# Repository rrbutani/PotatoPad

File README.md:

# PotatoPad
A (potato-y) portable game console made using the TM4C Launchpad, duct tape, and magic.

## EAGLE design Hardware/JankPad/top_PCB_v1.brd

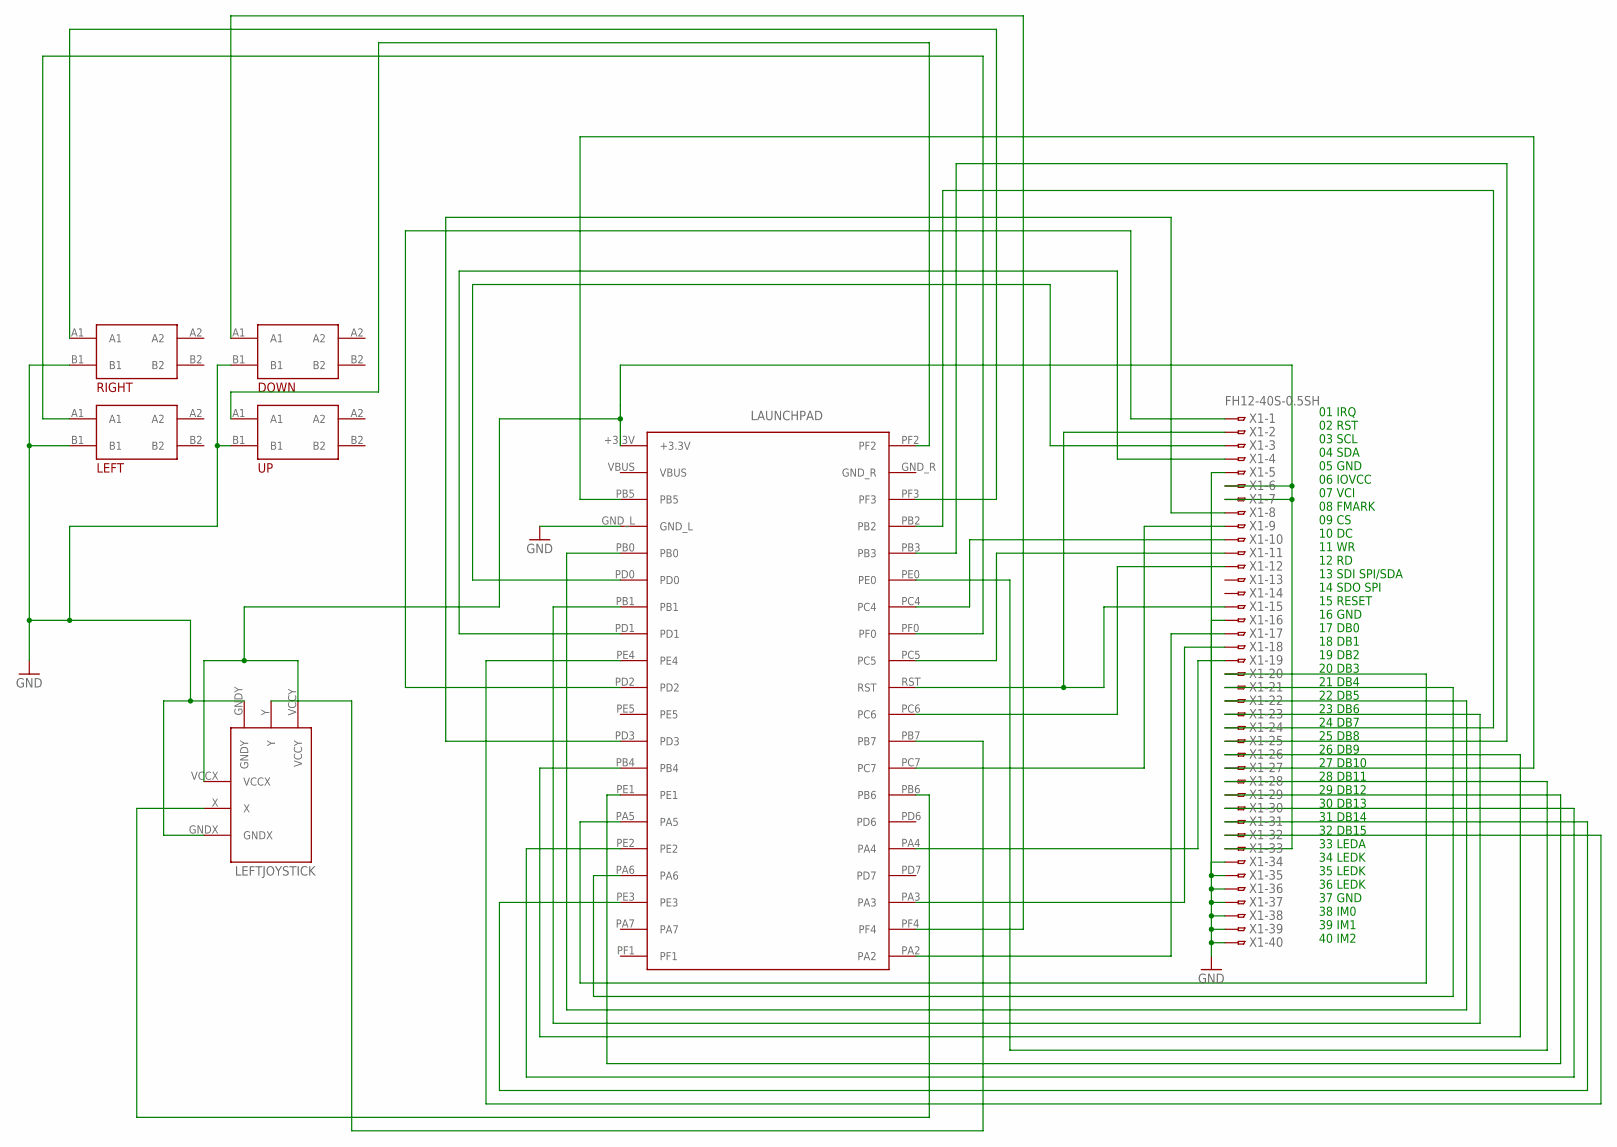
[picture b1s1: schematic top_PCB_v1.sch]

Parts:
DOWN: TACTILEBUTTONTHROUGHHOLE; B3F-40XX-MOD
LAUNCHPAD: TM4CTM4C; 1_05X2MM
LEFT: TACTILEBUTTONTHROUGHHOLE; B3F-40XX-MOD
LEFTJOYSTICK: JOYSTICKADAFRUIT; JOYSTICK
RIGHT: TACTILEBUTTONTHROUGHHOLE; B3F-40XX-MOD
UP: TACTILEBUTTONTHROUGHHOLE; B3F-40XX-MOD
X1: FH12-40S-0.5SH

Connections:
GND: DOWN.B1, LAUNCHPAD.GND_L, LEFT.B1, LEFTJOYSTICK.GNDX, LEFTJOYSTICK.GNDY, RIGHT.B1, UP.B1, X1.5, X1.16, X1.34, X1.35, X1.36, X1.37, X1.38, X1.39, X1.40
GND_R: LAUNCHPAD.GND_R
unnamed: LAUNCHPAD.PD3, X1.8
unnamed: LAUNCHPAD.RST, X1.2, X1.15
unnamed: LAUNCHPAD.PC4, X1.10
unnamed: LAUNCHPAD.PC5, X1.11
unnamed: LAUNCHPAD.PC6, X1.12
unnamed: LAUNCHPAD.PC7, X1.9
unnamed: LAUNCHPAD.PA2, X1.17
unnamed: LAUNCHPAD.PF2, UP.A1
unnamed: LAUNCHPAD.PD0, X1.3
unnamed: LAUNCHPAD.PD1, X1.4
unnamed: LAUNCHPAD.PD2, X1.1
unnamed: LAUNCHPAD.PA3, X1.18
unnamed: LAUNCHPAD.PA4, X1.19
unnamed: LAUNCHPAD.PA5, X1.20
unnamed: LAUNCHPAD.PA6, X1.21
unnamed: LAUNCHPAD.PB0, X1.22
unnamed: LAUNCHPAD.PB1, X1.23
unnamed: LAUNCHPAD.PB2, X1.24
unnamed: LAUNCHPAD.PB3, X1.25
unnamed: LAUNCHPAD.PB4, X1.26
unnamed: LAUNCHPAD.PB5, X1.27
unnamed: LAUNCHPAD.PE0, X1.28
unnamed: LAUNCHPAD.PE1, X1.29
unnamed: LAUNCHPAD.PE2, X1.30
unnamed: LAUNCHPAD.PE3, X1.31
unnamed: LAUNCHPAD.PE4, X1.32
unnamed: LAUNCHPAD.PB6, LEFTJOYSTICK.X
unnamed: LAUNCHPAD.PF0, LEFT.A1
unnamed: LAUNCHPAD.PF3, RIGHT.A1
unnamed: LAUNCHPAD.+3.3V, LEFTJOYSTICK.VCCX, LEFTJOYSTICK.VCCY, X1.6, X1.7, X1.33
unnamed: DOWN.A1, LAUNCHPAD.PF4
unnamed: LAUNCHPAD.PB7, LEFTJOYSTICK.Y
VBUS: LAUNCHPAD.VBUS

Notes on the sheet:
01 IRQ 02 RST 03 SCL 04 SDA 05 GND 06 IOVCC 07 VCI 08 FMARK 09 CS 10 DC 11 WR 12 RD 13 SDI SPI/SDA 14 SDO SPI 15 RESET 16 GND 17 DB0 18 DB1 19 DB2 20 DB3 21 DB4 22 DB5 23 DB6 24 DB7 25 DB8 26 DB9 27 DB10 28 DB11 29 DB12 30 DB13 31 DB14 32 DB15 33 LEDA 34 LEDK 35 LEDK 36 LEDK 37 GND 38 IM0 39 IM1 40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

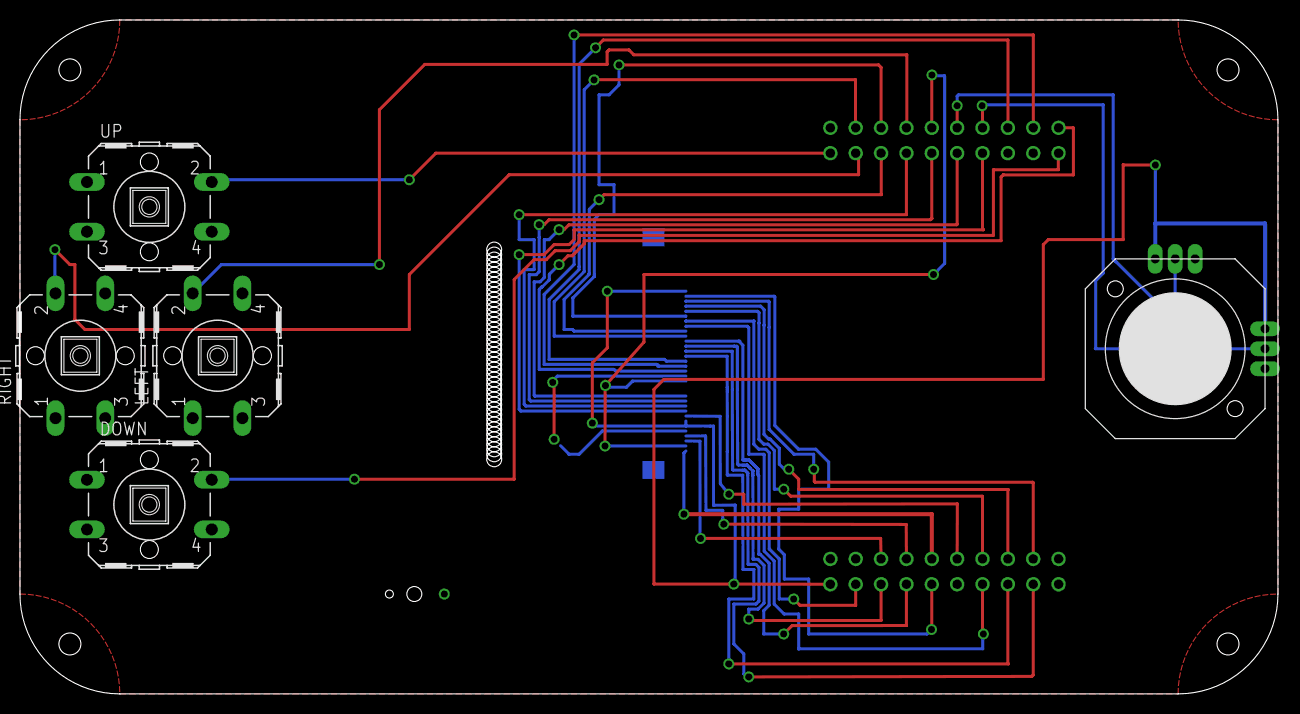
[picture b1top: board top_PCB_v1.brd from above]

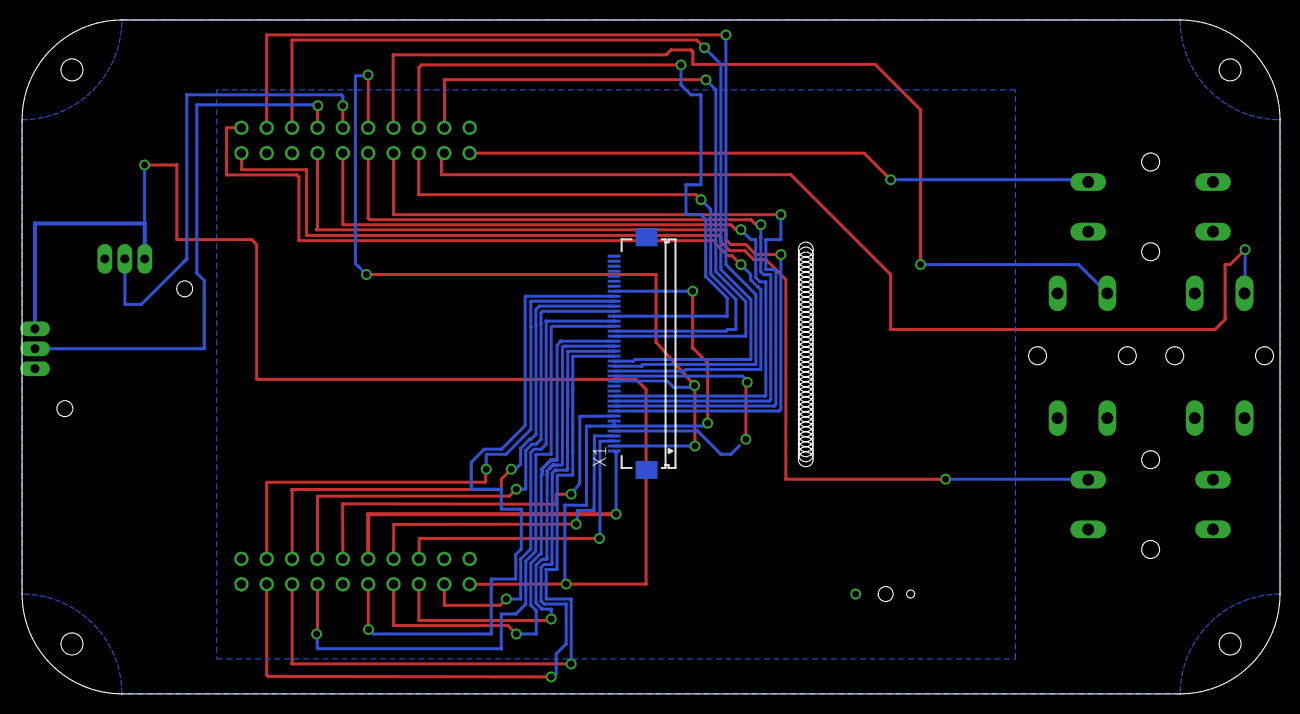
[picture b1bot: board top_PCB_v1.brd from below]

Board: 2 copper layers, 126.0 x 67.5 mm, 7 parts (2 on the bottom side), 33 nets.

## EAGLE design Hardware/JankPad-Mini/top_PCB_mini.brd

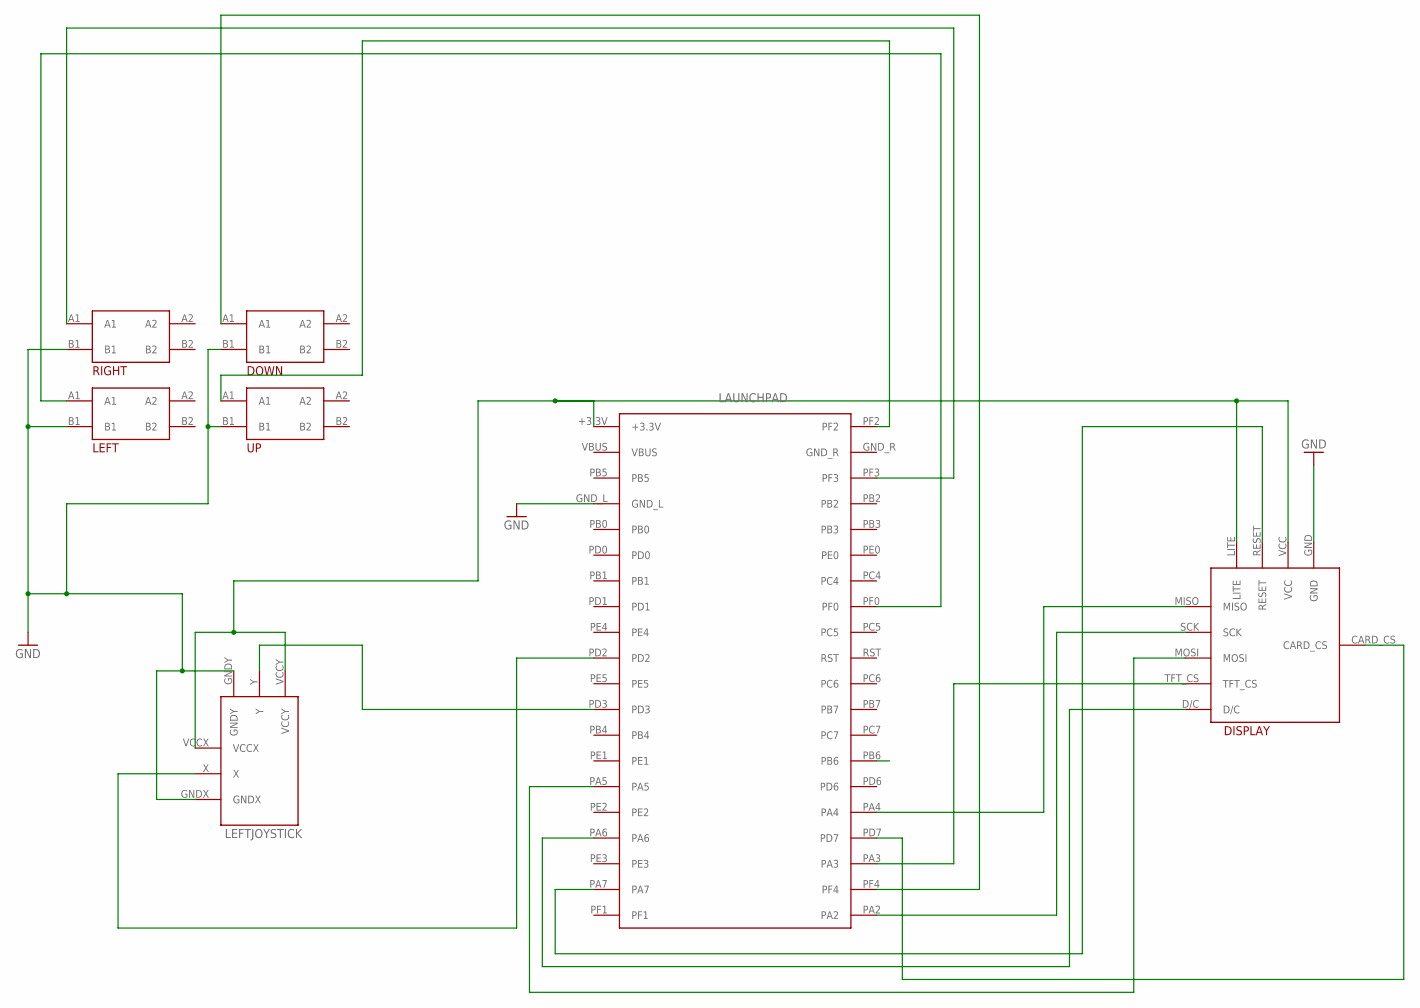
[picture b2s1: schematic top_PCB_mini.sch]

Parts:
DISPLAY: ADAFRUITST7735R_18
DOWN: TACTILEBUTTONTHROUGHHOLE; B3F-40XX-MOD
LAUNCHPAD: TM4CTM4C; 1_05X2MM
LEFT: TACTILEBUTTONTHROUGHHOLE; B3F-40XX-MOD
LEFTJOYSTICK: JOYSTICKADAFRUIT; JOYSTICK
RIGHT: TACTILEBUTTONTHROUGHHOLE; B3F-40XX-MOD
UP: TACTILEBUTTONTHROUGHHOLE; B3F-40XX-MOD

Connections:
GND: DISPLAY.GND, DOWN.B1, LAUNCHPAD.GND_L, LEFT.B1, LEFTJOYSTICK.GNDX, LEFTJOYSTICK.GNDY, RIGHT.B1, UP.B1
GND_R: LAUNCHPAD.GND_R
unnamed: DISPLAY.RESET, LAUNCHPAD.PA7
unnamed: DISPLAY.D/C, LAUNCHPAD.PA6
unnamed: DISPLAY.CARD_CS, LAUNCHPAD.PD7
unnamed: DISPLAY.TFT_CS, LAUNCHPAD.PA3
unnamed: DISPLAY.MOSI, LAUNCHPAD.PA5
unnamed: DISPLAY.SCK, LAUNCHPAD.PA2
unnamed: DISPLAY.MISO, LAUNCHPAD.PA4
unnamed: LAUNCHPAD.PF2, UP.A1
unnamed: LAUNCHPAD.PD2, LEFTJOYSTICK.X
unnamed: LAUNCHPAD.PD3, LEFTJOYSTICK.Y
unnamed: LAUNCHPAD.PF0, LEFT.A1
unnamed: LAUNCHPAD.PF3, RIGHT.A1
unnamed: DISPLAY.LITE, DISPLAY.VCC, LAUNCHPAD.+3.3V, LEFTJOYSTICK.VCCX, LEFTJOYSTICK.VCCY
unnamed: DOWN.A1, LAUNCHPAD.PF4
VBUS: LAUNCHPAD.VBUS

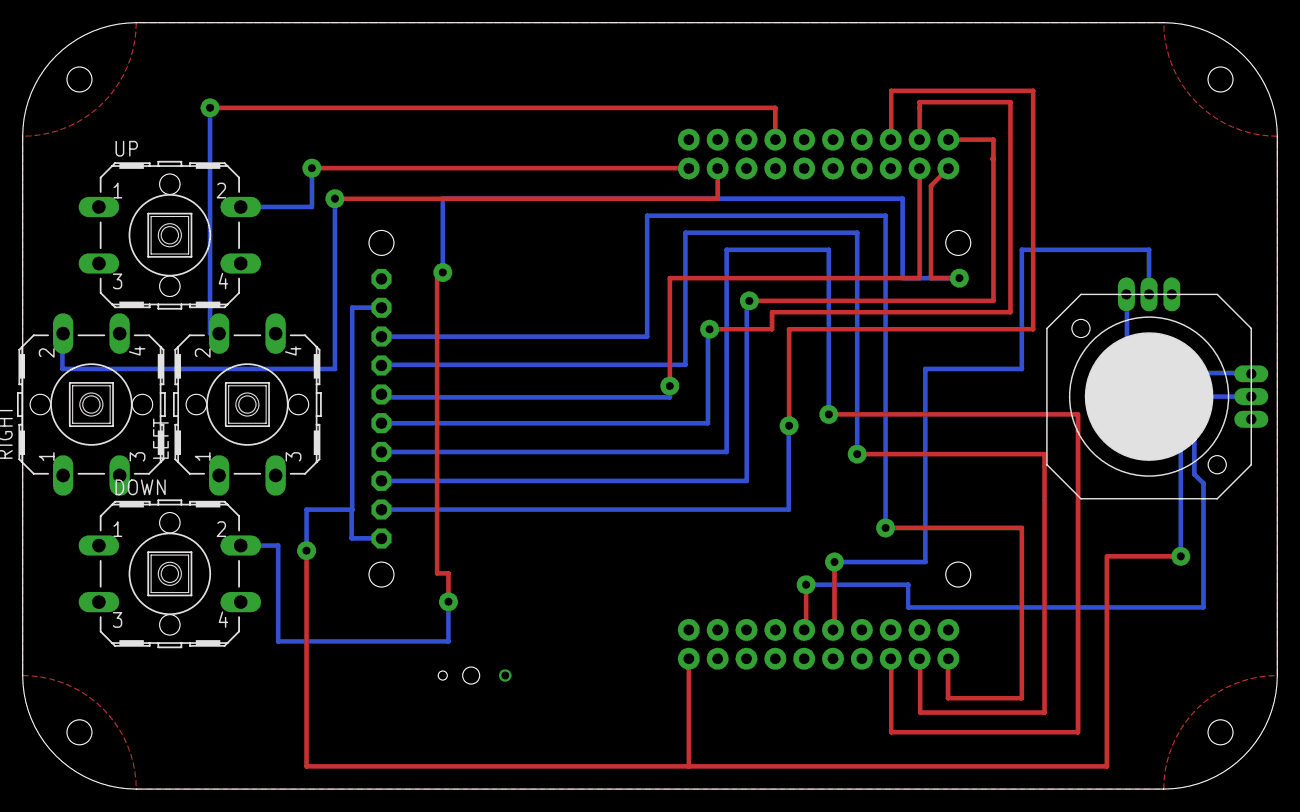
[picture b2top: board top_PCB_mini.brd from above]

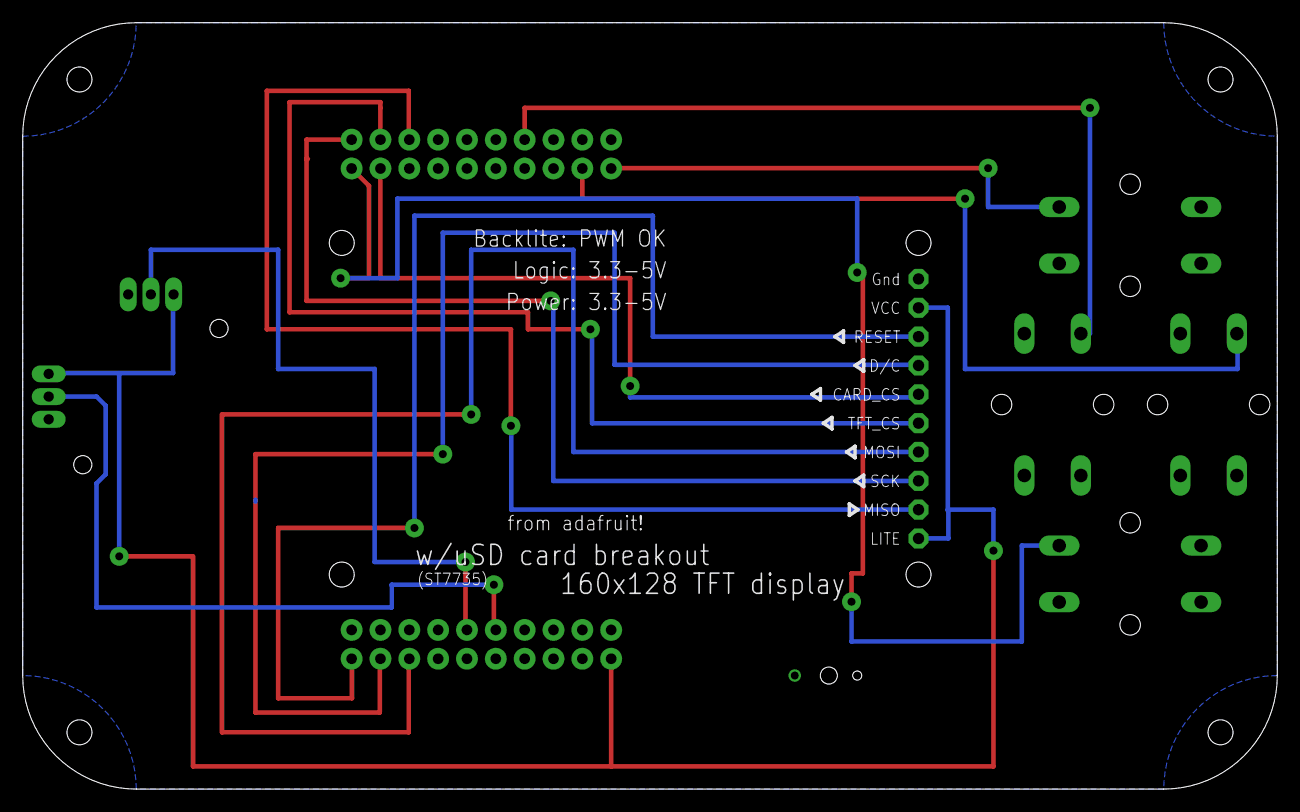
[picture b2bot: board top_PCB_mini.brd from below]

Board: 2 copper layers, 110.5 x 67.5 mm, 7 parts (2 on the bottom side), 15 nets.

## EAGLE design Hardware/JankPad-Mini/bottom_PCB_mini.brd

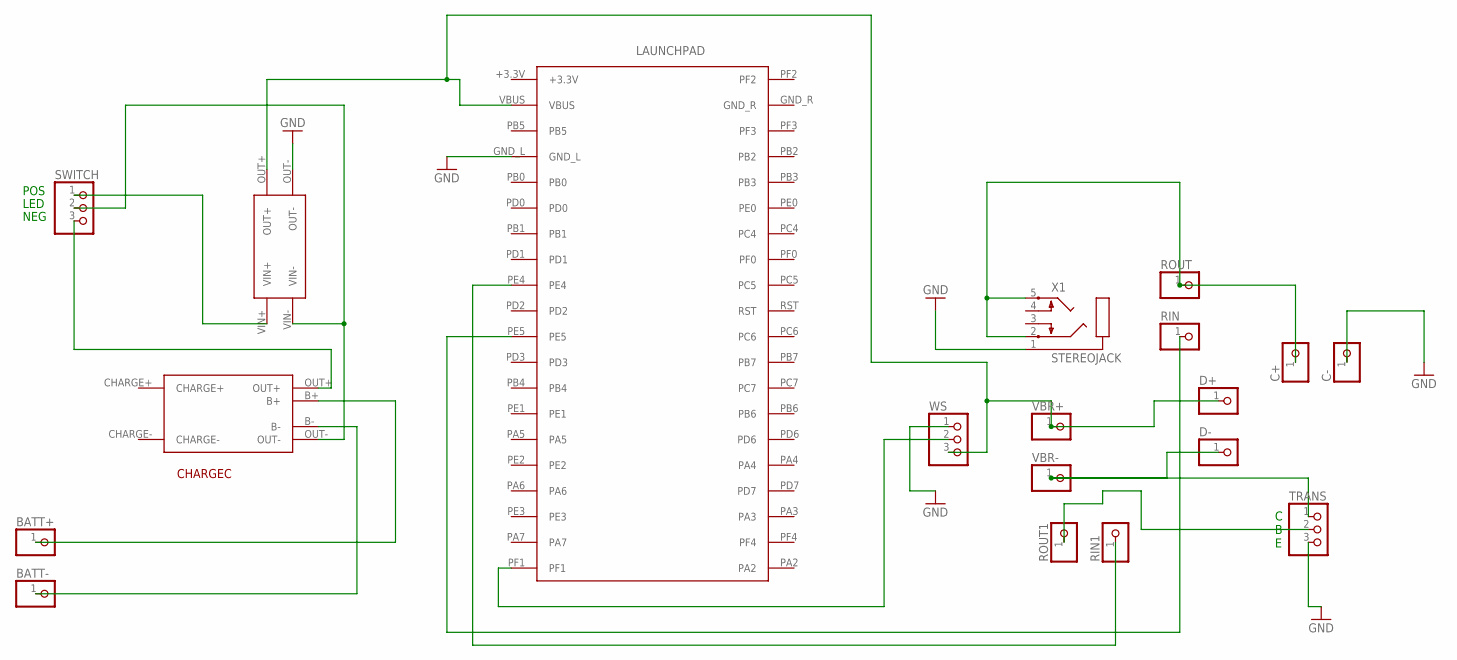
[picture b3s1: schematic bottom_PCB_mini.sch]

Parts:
BATT+: PINHD-1X1CB; 1X01-CLEANBIG
BATT-: PINHD-1X1CB; 1X01-CLEANBIG
C+: PINHD-1X1CB; 1X01-CLEANBIG
C-: PINHD-1X1CB; 1X01-CLEANBIG
CHARGEC: 18650CCEBAY
D+: PINHD-1X1CB; 1X01-CLEANBIG
D-: PINHD-1X1CB; 1X01-CLEANBIG
LAUNCHPAD: TM4CTM4C; 1_05X2MM
RIN, RIN1: PINHD-1X1CB; 1X01-CLEANBIG
ROUT, ROUT1: PINHD-1X1CB; 1X01-CLEANBIG
SWITCH: PINHD-1X3CB; 1X03-CLEANBIG
TRANS: PINHD-1X3CB; 1X03-CLEANBIG
VBR+: PINHD-1X1CB; 1X01-CLEANBIG
VBR-: PINHD-1X1CB; 1X01-CLEANBIG
VREG: MT3608_EBAY
WS: PINHD-1X3CB; 1X03-CLEANBIG
X1: STEREOJACK; STX3100

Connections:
+3.3V: LAUNCHPAD.+3.3V
GND: C-.1, LAUNCHPAD.GND_L, TRANS.3, VREG.OUT-, WS.1, X1.1
GND_R: LAUNCHPAD.GND_R
unnamed: BATT-.1, CHARGEC.B-
unnamed: BATT+.1, CHARGEC.B+
unnamed: CHARGEC.OUT-, SWITCH.2, VREG.VIN-
unnamed: CHARGEC.OUT+, SWITCH.3
unnamed: SWITCH.1, VREG.VIN+
unnamed: C+.1, ROUT.1, X1.2, X1.5
unnamed: D+.1, LAUNCHPAD.VBUS, VBR+.1, VREG.OUT+, WS.3
unnamed: LAUNCHPAD.PF1, WS.2
unnamed: LAUNCHPAD.PE5, RIN.1
unnamed: LAUNCHPAD.PE4, RIN1.1
unnamed: ROUT1.1, TRANS.2
unnamed: D-.1, TRANS.1, VBR-.1

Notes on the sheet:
POS
LED
NEG
C B E

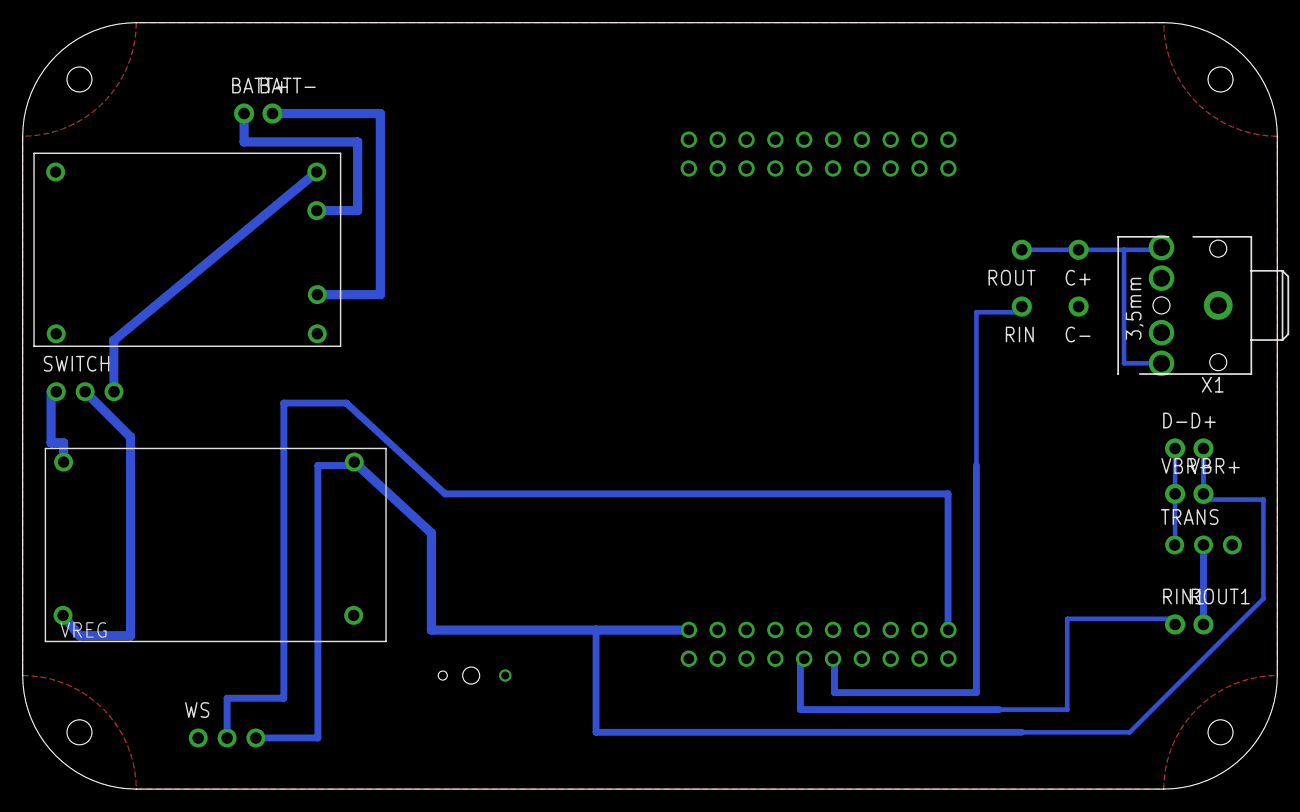
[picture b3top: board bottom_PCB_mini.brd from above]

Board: 2 copper layers, 110.5 x 67.5 mm, 19 parts (1 on the bottom side), 13 nets.

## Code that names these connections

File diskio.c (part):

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/-------------------------------------------------------------------------*/
// converted to TM4C123
// Feb 22, 2016
// added PB0 as a choice for SDC CS
#include <stdint.h>
#include <stdio.h>
//#include "../../contrib/tm4c123gh6pm.h"
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#define SDC_CS_PB0 0
#define SDC_CS_PD7 1

// SDC CS is PD7 or PB0 , TFT CS is PA3
// to change CS to another GPIO, change SDC_CS and CS_Init
// **********ST7735 TFT and SDC*******************
// ST7735
// 1  ground
// 2  Vcc +3.3V
// 3  PA7 TFT reset
// 4  PA6 TFT data/command
// 5  PD7/PB0 SDC_CS, active low to enable SDC
// 6  PA3 TFT_CS, active low to enable TFT
// 7  PA5 MOSI SPI data from microcontroller to TFT or SDC
// 8  PA2 Sclk SPI clock from microcontroller to TFT or SDC
// 9  PA4 MOSO SPI data from SDC to microcontroller
// 10 Light, backlight connected to +3.3 V

// **********wide.hk ST7735R*******************
// Silkscreen Label (SDC side up; LCD side down) - Connection
// VCC  - +3.3 V
// GND  - Ground
// !SCL - PA2 Sclk SPI clock from microcontroller to TFT or SDC
// !SDA - PA5 MOSI SPI data from microcontroller to TFT or SDC
// DC   - PA6 TFT data/command
// RES  - PA7 TFT reset
// CS   - PA3 TFT_CS, active low to enable TFT
// *CS  - PD7/PB0 SDC_CS, active low to enable SDC
// MISO - PA4 MISO SPI data from SDC to microcontroller
// SDA   (NC) I2C data for ADXL345 accelerometer
// SCL   (NC) I2C clock for ADXL345 accelerometer
// SDO   (NC) I2C alternate address for ADXL345 accelerometer
// Backlight + - Light, backlight connected to +3.3 V

#define TFT_CS           (*((volatile uint32_t *)0x40004020))
#define TFT_CS_LOW       0           // CS controlled by software PA3
#define TFT_CS_HIGH      0x08
#if SDC_CS_PD7
// PD7 output used for SDC CS
#define SDC_CS           (*((volatile uint32_t *)0x40007200))
#define SDC_CS_LOW       0           // CS controlled by software
#define SDC_CS_HIGH      0x80
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  SYSCTL_RCGCGPIO_R |= 0x08;            // activate clock for Port D
  while((SYSCTL_PRGPIO_R&0x08) == 0){}; // allow time for clock to stabilize
  GPIO_PORTD_LOCK_R = 0x4C4F434B;       // unlock GPIO Port D
  GPIO_PORTD_CR_R = 0xFF;               // allow changes to PD7-0
  // only PD7 needs to be unlocked, other bits can't be locked
  GPIO_PORTD_DIR_R |= 0x80;             // make PD7 out
  GPIO_PORTD_AFSEL_R &= ~0x80;          // disable alt funct on PD7
  GPIO_PORTD_DR4R_R |= 0x80;            // 4mA drive on outputs
  GPIO_PORTD_PUR_R |= 0x80;             // enable weak pullup on PD7
  GPIO_PORTD_DEN_R |= 0x80;             // enable digital I/O on PD7
                                        // configure PD7 as GPIO
  GPIO_PORTD_PCTL_R = (GPIO_PORTD_PCTL_R&0x0FFFFFFF)+0x00000000;
  GPIO_PORTD_AMSEL_R &= ~0x80;          // disable analog functionality on PD7
  SDC_CS = SDC_CS_HIGH;
}
#endif
// PB0 output used for SDC CS
#if SDC_CS_PB0
#define SDC_CS           (*((volatile uint32_t *)0x40005004))
#define SDC_CS_LOW       0           // CS controlled by software
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void CS_Init(void){
  SYSCTL_RCGCGPIO_R |= 0x02;            // activate clock for Port B
  while((SYSCTL_PRGPIO_R&0x02) == 0){}; // allow time for clock to stabilize
  GPIO_PORTB_DIR_R |= 0x01;             // make PB0 out
  GPIO_PORTB_AFSEL_R &= ~0x01;          // disable alt funct on PB0
  GPIO_PORTB_DR4R_R |= 0x01;            // 4mA drive on outputs
  GPIO_PORTB_PUR_R |= 0x01;             // enable weak pullup on PB0
  GPIO_PORTB_DEN_R |= 0x01;             // enable digital I/O on PB0
                                        // configure PB0 as GPIO
  GPIO_PORTB_PCTL_R = (GPIO_PORTB_PCTL_R&0xFFFFFFF0)+0x00000000;
  GPIO_PORTB_AMSEL_R &= ~0x01;          // disable analog functionality on PB0
  SDC_CS = SDC_CS_HIGH;
}
#endif
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  // initialize Port A
  SYSCTL_RCGCGPIO_R |= 0x01;            // activate clock for Port A
  while((SYSCTL_PRGPIO_R&0x01) == 0){}; // allow time for clock to stabilize
  GPIO_PORTA_DIR_R |= 0x08;             // make PA3 out
  GPIO_PORTA_AFSEL_R |= 0x34;           // enable alt funct on PA2,4,5
  GPIO_PORTA_AFSEL_R &= ~0x08;          // disable alt funct on PA3
  GPIO_PORTA_DR4R_R |= 0xFC;            // 4mA drive on outputs
  GPIO_PORTA_PUR_R |= 0x3C;             // enable weak pullup on PA2,3,4,5
  GPIO_PORTA_DEN_R |= 0x3C;             // enable digital I/O on PA2,3,4,5
                                        // configure PA2,4,5 as SSI
  GPIO_PORTA_PCTL_R = (GPIO_PORTA_PCTL_R&0xFF00F0FF)+0x00220200;
                                        // configure PA3 as GPIO
  GPIO_PORTA_PCTL_R = (GPIO_PORTA_PCTL_R&0xFFFF0FFF)+0x00000000;
  GPIO_PORTA_AMSEL_R &= ~0x3C;          // disable analog functionality on PA2,3,4,5
  TFT_CS = TFT_CS_HIGH;                 // disable LCD
  // initialize SSI0
  SYSCTL_RCGCSSI_R |= 0x01;             // activate clock for SSI0
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  SSI0_CR1_R |= SSI_CR1_SSE;            // enable SSI
}
//void MakeTxhigh(void){
//  GPIO_PORTA_AFSEL_R &= ~0x10;          // disable alt funct on PA4
//  GPIO_PORTA_PCTL_R = (GPIO_PORTA_PCTL_R&0xFFF0FFFF);
//  GPIO_PORTA_DATA_R |= 0x10;            // PA4 high
//}
//void MakeTxSSI(void){
//  GPIO_PORTA_AFSEL_R |= 0x10;           // enable alt funct on PA4
//  GPIO_PORTA_PCTL_R = (GPIO_PORTA_PCTL_R&0xFFF0FFFF)+0x000F0000;
//}

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
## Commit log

2017-03-25 First Post
2017-03-25 updated deploy to put site in root dir
2017-03-25 No testing like prod testing
2017-03-25 remove chalk folder, stop trying to be clever, etc.
2017-03-25 Revert "remove chalk folder, stop trying to be clever, etc."
    This reverts commit 4f8f939f1c4b16423efda1f6634ac99b731f3658.
2017-03-25 Maybe?
2017-03-25 Maybe?2
2017-03-25 Maybe?3
2017-03-25 basic structure
2017-03-25 Added some useful documentation/references
2017-03-25 Added some useful documentation/references (#1)
2017-03-27 Part 1
    Routines not implemented yet, but the basics are all present.
    (Still untested though)
2017-03-27 Part 2
    More structure, stilled untested.
    (Contains test code)
2017-03-27 Testing begins...
    Contains very important fixes that actually make: a) Keil flash the
    board correctly, b) the Launchpad not crash on start, and c) the
    Launchpad not brick everytime it's flashed.
    Finally started testing; it seems like the port input/output logic is
    borked. Also, I clearly don't understand how PCTL works.
    That's all for tonight.
2017-03-29 Bugs!
    http://bit.ly/1hQ8erg
2017-03-29 Save State
2017-04-04 Bunch of changes
    Formatting was changed from tabs to spaces at some point so the diffs are all messed up for this commit; please ignore.
2017-04-04 Optimized display driver prototyping
2017-04-04 Checkpoint: Working on gnu build system instead of Keil
2017-04-04 Use openocd in repo as opposed to building our own
2017-04-08 Modified SD module from to run independently of LCD and remap port
2017-04-17 GCC Build Environment script now (partially?) complete and battle tested on Ubuntu 16.04/equivalent
    (slow progress)
2017-04-25 Graphics update
    3D render pipeline
    -binary space partition tree navigation
    -backface culling
    -camera transform
    -clipping
    -perspective transform
2017-04-29 Collision update
    - Implment collision using vector calculation
    - Handle transparent sprites
    - Vastly cleaned up BSP navigation
    - Seperate vocal length adjusting to aspect ratio
2017-04-29 Organization update
    - Reorganize to promote modularity
    - Fix texture warping at close range; still needs work
2017-04-29 Checkpoint/misc changes
2017-04-29 Fix udev rule syntax
2017-04-29 GNU Build System Checkpoint
2017-04-29 Once again... (#3)
    * Adding Eagle files for the JankPad
    * ...and the rest of the Eagle files.
2017-04-29 Housekeeping
2017-04-29 More housekeeping
2017-04-30 Misc
2017-04-30 Added other useful datasheets
2017-04-30 PWM, Round 1
    Much jank, need slep
2017-05-02 HUD update
    - Added HUD and title screen
    - Added gun fire when shooting
    - Added enemy shooting logic
2017-05-02 Snapshot
2017-05-02 PWM Audio using SD Card IO is now working!
    There's a script to convert the output of the .txt files that Dr. Y's
    WavConv script generates into the needed format for this program.
    Right now, it's still choppy which is more noticable with headphones...
    Also, this breaks with the changes to the ST7735R initialization and
    this needs to be packaged properly and moved off of Systick.
2017-05-02 New PCB for ST7735R Setup
    (I failed?)
2017-05-02 Bottom PCB for the mini
    Potatoes!
2017-05-03 bugs everywhere
2017-05-03 more bugs
2017-05-03 Backup update
    - added input
    - added audio
    - update menu and end screen
2017-05-03 Sound update
    - Coexistance between LCD and SD card at different speed
    - Background music
2017-05-03 4 AM.
    (Snapshot)
2017-05-03 Basic operation update
    - Sound effect
2017-05-03 Snapshot!!
2017-05-05 Organization update
    - Reorganized files
    - Partially fixed invisible enemies
2017-05-05 Optimization update
    - Up clock speed to 40 MHz
    - Simplify organization using common.h
2017-05-05 Misc Changes
    Audio was cleaned up; nothing else of consequence
2017-05-05 Collision patch
    - Improved collision
2017-05-05 Revise Sound for SFX on ROM and multiple channels.
2017-05-05 Update .gitignore / Clean up junk
2017-05-05 Repair sct file
2017-05-05 Add Ending Song
2017-05-05 Restructuring...
    (In Preparation for Merge)
2017-05-05 More structuring
2017-05-05 Preparing for merge
2017-05-05 Fix Merge issues
2017-05-05 Added Reset and more ending songs
2017-05-05 Files for top/bottom cover
    svg file for laser cutting, untested
    (Also updated some gitignores)
2017-05-05 Last minute changes
    DXF for top/bottom cover
    Graphics collision updates
    C'est fini et nous finissons.
2017-05-05 Jank -> Potato (Rebranding and public release) Jank is dead, long live Potato.
2017-05-05 Public Release!
2017-05-06 Update README.md
    Public Release imminent!
2017-05-06 fix derp
2017-05-06 fix derp [ci skip]

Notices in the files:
diskio.c:
Copyright (C) 2014, ChaN, all right reserved.
